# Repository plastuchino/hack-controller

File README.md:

initial commit readme of my first hardware project

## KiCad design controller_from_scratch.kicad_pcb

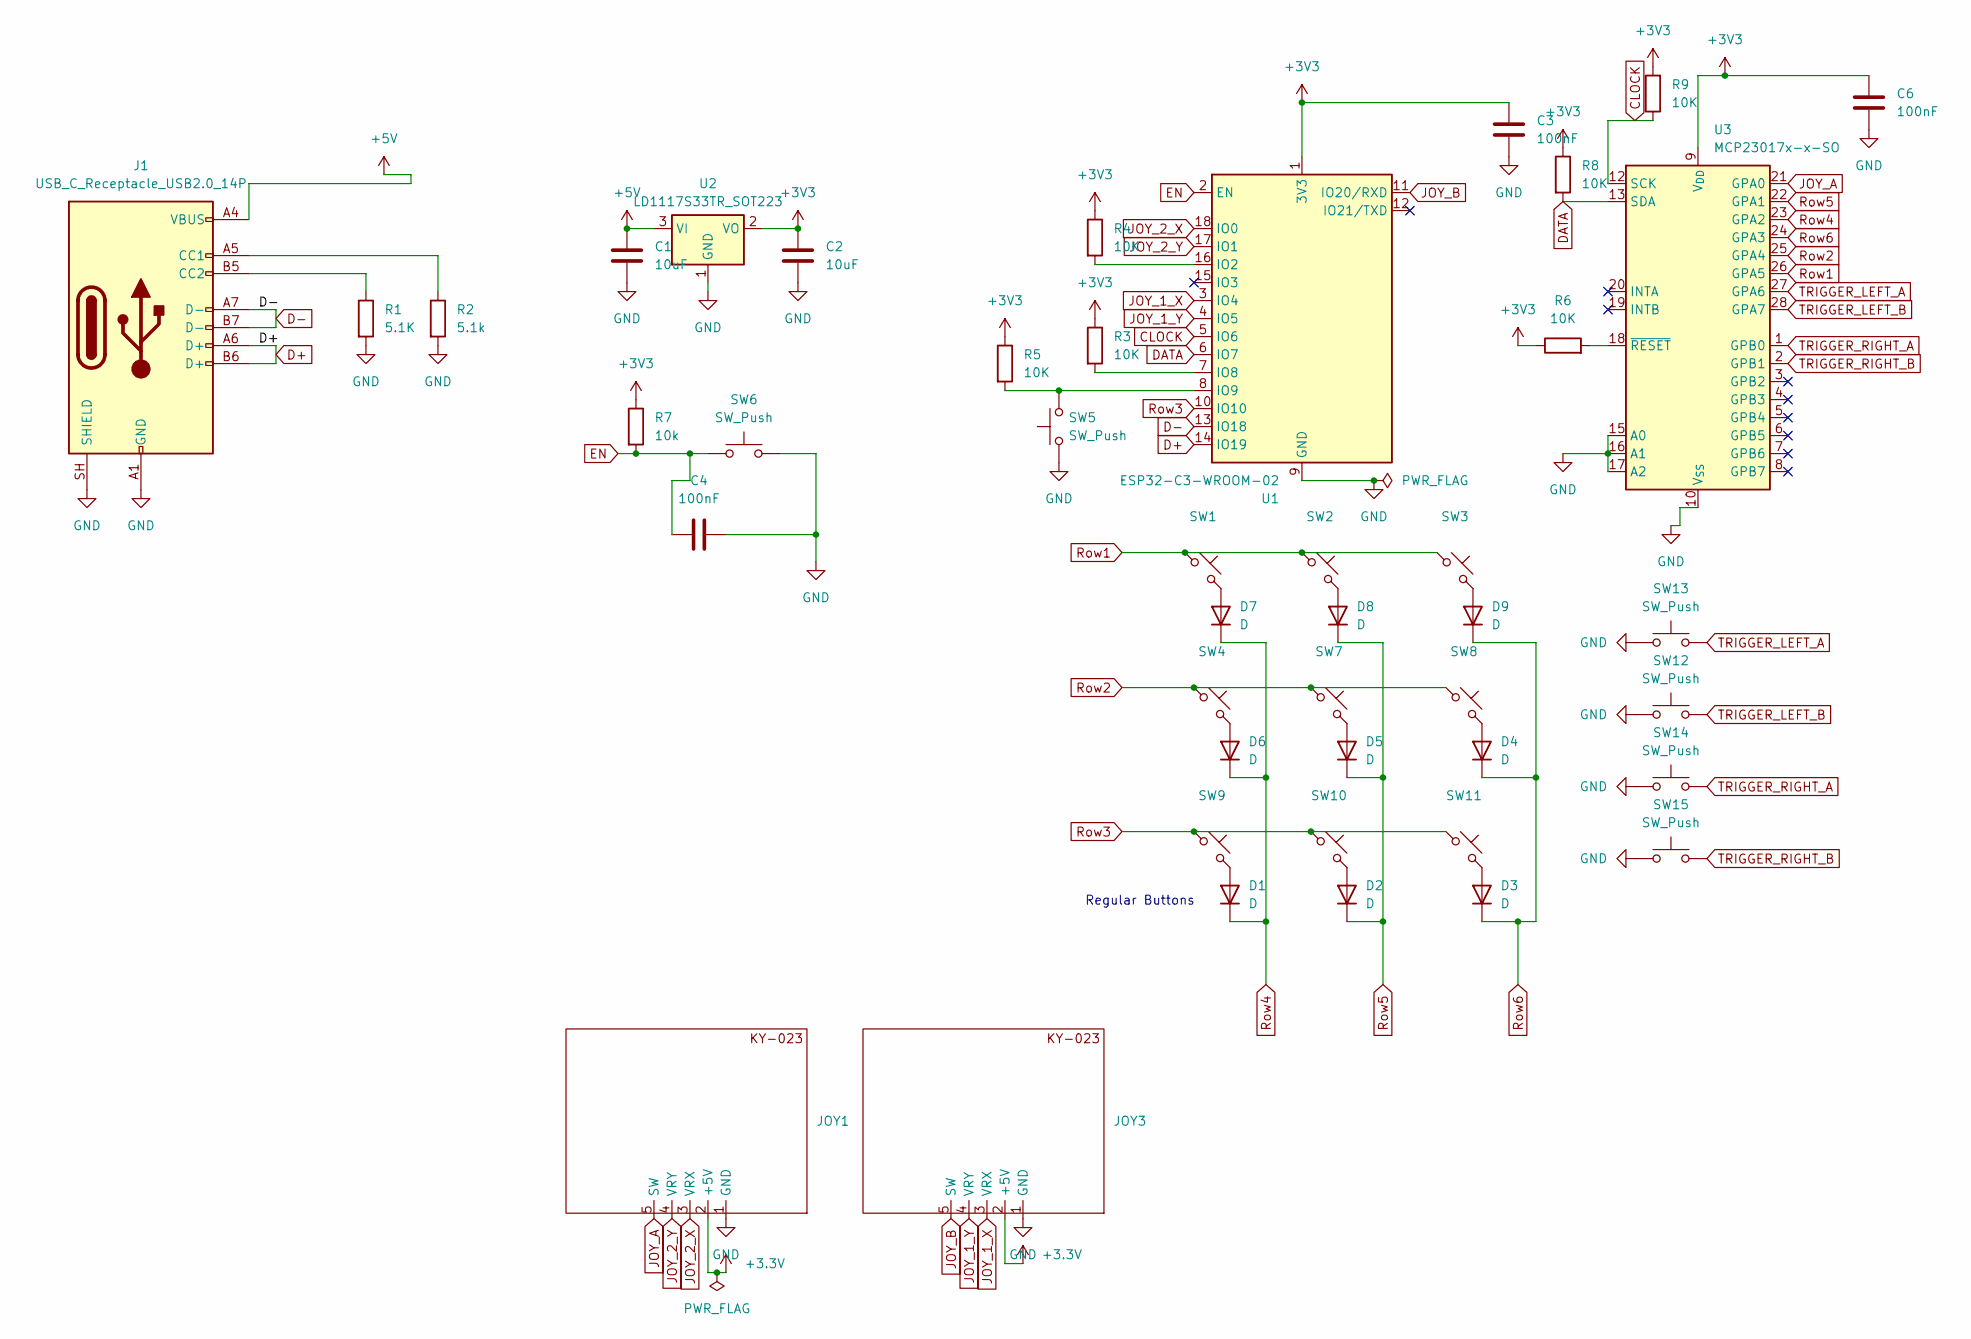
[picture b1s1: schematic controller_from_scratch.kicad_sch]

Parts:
C1, C2: 10uF; C_1206_3216Metric
C3, C4, C6: 100nF; C_1206_3216Metric
D1, D2, D3, D4, D5, D6, D7, D8, D9: D; D_1206_3216Metric_Pad1.42x1.75mm_HandSolder
J1: USB_C_Receptacle_USB2.0_14P; USB_C_Receptacle_HRO_TYPE-C-31-M-12
JOY1, JOY3: PinHeader_1x05_P2.54mm_Vertical
R1: 5.1K; R_1206_3216Metric_Pad1.30x1.75mm_HandSolder
R2: 5.1k; R_1206_3216Metric_Pad1.30x1.75mm_HandSolder
R3, R4, R5, R6, R8, R9: 10K; R_1206_3216Metric_Pad1.30x1.75mm_HandSolder
R7: 10k; R_1206_3216Metric_Pad1.30x1.75mm_HandSolder
SW1, SW2, SW3, SW4, SW7, SW8, SW9, SW10, SW11: SW_Push_45deg; PinHeader_2x01_P2.54mm_Vertical
SW5, SW6, SW12, SW13, SW14, SW15: SW_Push; PinHeader_2x01_P2.54mm_Vertical
U1: ESP32-C3-WROOM-02
U2: LD1117S33TR_SOT223; SOT-223-3_TabPin2
U3: MCP23017x-x-SO; SOIC-28W_7.5x17.9mm_P1.27mm

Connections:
+3.3V: JOY1.2 (+5V), JOY3.2 (+5V)
+3V3: C2.2, C3.2, C6.2, R3.1, R4.1, R5.1, R6.1, R7.1, R8.1, R9.2, U1.1 (3V3), U2.2 (VO), U3.9 (V_{DD})
+5V: C1.1, J1.A4 (VBUS), J1.A9 (VBUS), J1.B4 (VBUS), J1.B9 (VBUS), U2.3 (VI)
CLOCK: R9.1, U1.5 (IO6), U3.12 (SCK)
D+: J1.A6 (D+), J1.B6 (D+), U1.14 (IO19)
D-: J1.A7 (D-), J1.B7 (D-), U1.13 (IO18)
DATA: R8.2, U1.6 (IO7), U3.13 (SDA)
EN: C4.2, R7.2, SW6.1, U1.2 (EN)
GND: C1.2, C2.1, C3.1, C4.1, C6.1, J1.A1 (GND), J1.A12 (GND), J1.B1 (GND), J1.B12 (GND), J1.SH (SHIELD), JOY1.1 (GND), JOY3.1 (GND), R1.2, R2.2, SW5.1, SW6.2, SW12.1, SW13.1, SW14.1, SW15.1, U1.9 (GND), U1.19 (GND), U2.1 (GND), U3.10 (V_{SS}), U3.15 (A0), U3.16 (A1), U3.17 (A2)
JOY_1_X: JOY3.3 (VRX), U1.3 (IO4)
JOY_1_Y: JOY3.4 (VRY), U1.4 (IO5)
JOY_2_X: JOY1.3 (VRX), U1.18 (IO0)
JOY_2_Y: JOY1.4 (VRY), U1.17 (IO1)
JOY_A: JOY1.5 (SW), U3.21 (GPA0)
JOY_B: JOY3.5 (SW), U1.11 (IO20/RXD)
unnamed: D1.2 (A), SW9.2
unnamed: D2.2 (A), SW10.2
unnamed: D3.2 (A), SW11.2
unnamed: D4.2 (A), SW8.2
unnamed: D5.2 (A), SW7.2
unnamed: D6.2 (A), SW4.2
unnamed: D7.2 (A), SW1.2
unnamed: D8.2 (A), SW2.2
unnamed: D9.2 (A), SW3.2
unnamed: J1.A5 (CC1), R2.1
unnamed: J1.B5 (CC2), R1.1
unnamed: R4.2, U1.16 (IO2)
unnamed: R3.2, U1.7 (IO8)
unnamed: R5.2, SW5.2, U1.8 (IO9)
unnamed: R6.2, U3.18 (~RESET)
Row1: SW1.1, SW2.1, SW3.1, U3.26 (GPA5)
Row2: SW4.1, SW7.1, SW8.1, U3.25 (GPA4)
Row3: SW9.1, SW10.1, SW11.1, U1.10 (IO10)
Row4: D1.1 (K), D6.1 (K), D7.1 (K), U3.23 (GPA2)
Row5: D2.1 (K), D5.1 (K), D8.1 (K), U3.22 (GPA1)
Row6: D3.1 (K), D4.1 (K), D9.1 (K), U3.24 (GPA3)
TRIGGER_LEFT_A: SW13.2, U3.27 (GPA6)
TRIGGER_LEFT_B: SW12.2, U3.28 (GPA7)
TRIGGER_RIGHT_A: SW14.2, U3.1 (GPB0)
TRIGGER_RIGHT_B: SW15.2, U3.2 (GPB1)

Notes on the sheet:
Regular Buttons

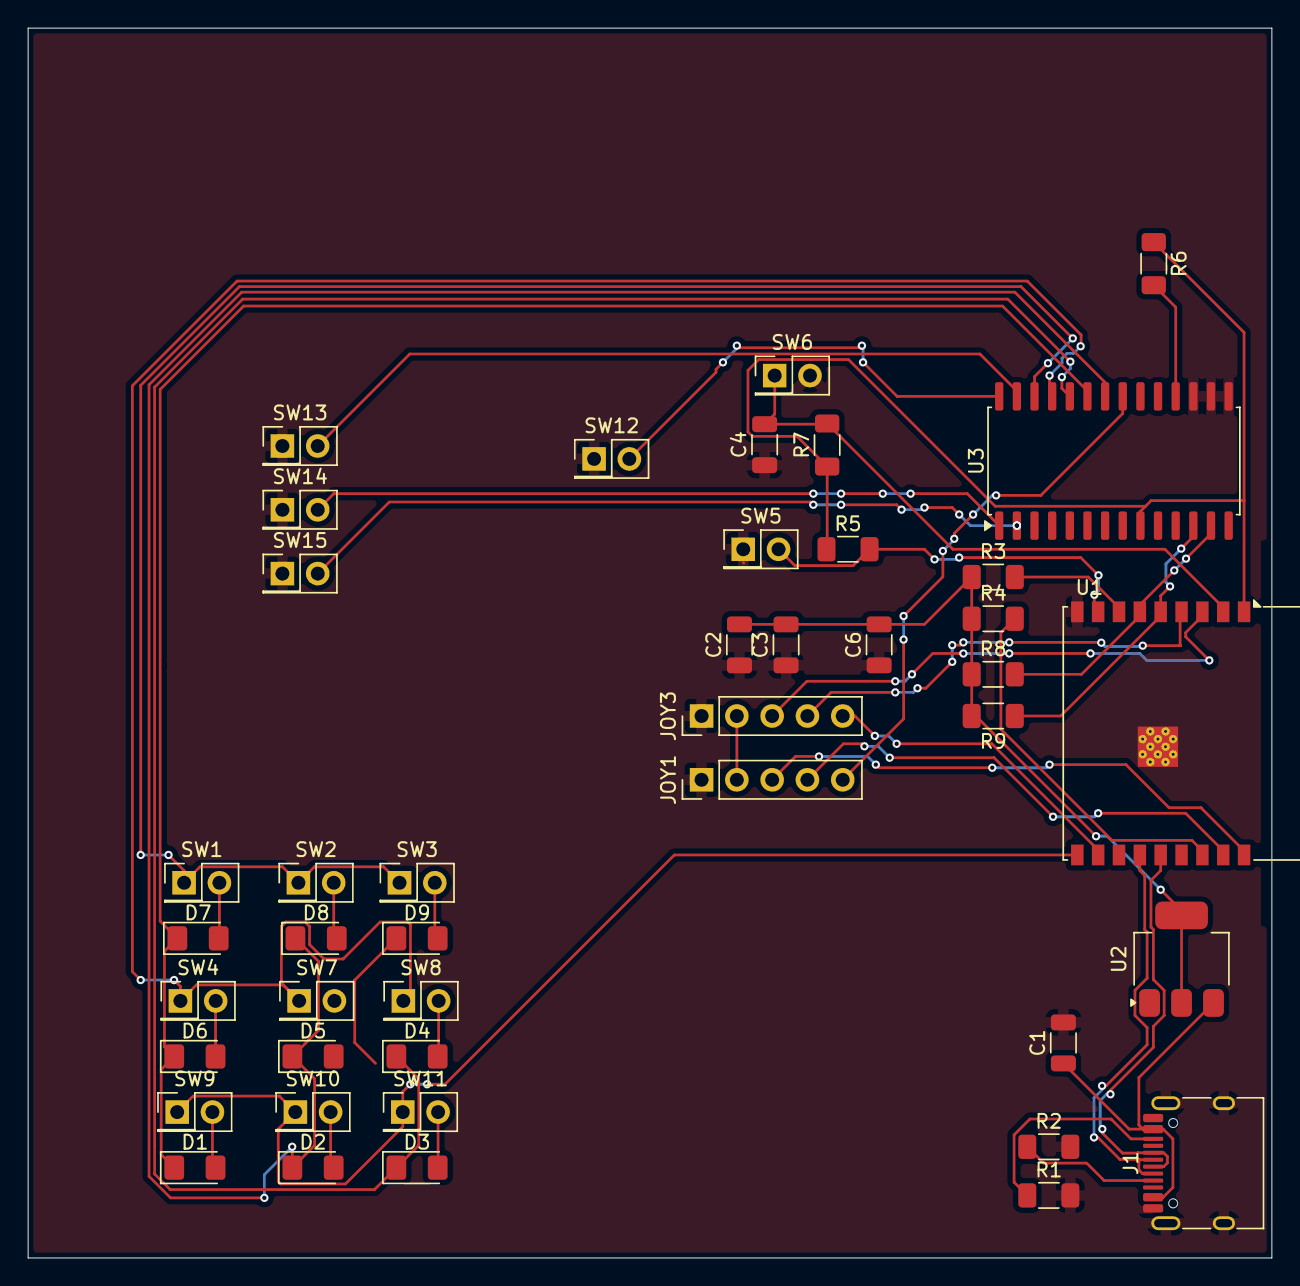
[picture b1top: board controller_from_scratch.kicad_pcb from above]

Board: 2 copper layers, 89.5 x 88.5 mm, 44 parts (0 on the bottom side), 40 nets.
